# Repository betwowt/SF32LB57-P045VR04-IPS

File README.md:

# SF32LB57-P045VR04-IPS

SF32LB57 + P045VR04-IPS（480×854，ST7701S，RGB565，FT6236 触摸）显示工程。

面板的 3 线 SPI 初始化由 `H743_RGB_Adapter` 板上的 PY32F002 完成；SF32LB57
只负责 DPI RGB565 时序、背光（GPIO）、触摸 I2C 和 READY/复位握手。这个分工与
`H743_RGB_Adapter.pdf` 的 “04 - PY32 display initialization” 页一致。

```mermaid
flowchart LR
    SF[SF32LB57<br/>DPI RGB565 480×854] -->|RGB565 + PCLK/HS/VS/DE| AD[H743_RGB_Adapter<br/>40P host J1]
    SF -->|BL_PWM| AD
    SF -->|I2C1 SCL/SDA, CTP_INT, CTP_RST| AD
    SF -->|可选 READY 输入| AD
    AD -->|J2/J7 40P| PANEL[P045VR04-IPS<br/>ST7701S + FT6236]
    PY[PY32F002<br/>3-wire SPI init] -->|SCL/SDA/CS/RST| PANEL
    PY -->|READY| AD
```

## 1. 目录结构

```
SF32LB57-P045VR04-IPS/
├─ board/sf32lb57-p045vr04/       # 板级定义（基于 sf32lb57-lcd_n16r8_dpi）
│  ├─ hcpu/                       # HCPU board.conf / Kconfig / rtconfig / mem map
│  ├─ acpu/ lcpu/                 # 多核工程占位配置
│  ├─ bsp_*.c board.h bsp_board.h # 从 sf32lb57-lcd_base 复制并按需修改
│  ├─ ptab.json                   # Flash 分区
│  └─ SConscript                  # 编译板级文件 + 面板/触摸驱动
├─ drivers/panel/p045vr04.c       # ST7701S RGB565 DPI 驱动（不做 SPI 初始化）
├─ drivers/touch/ft6236.c         # FT6236 / FT6x36 触摸驱动（12-bit X/Y）
├─ app/project/                   # SiFli/RT-Thread 工程（scons 构建入口）
│  └─ proj.conf                   # RT-Thread / Wi-Fi / Opus / LVGL 选项
├─ app/src/main.c                 # xiaozhi 入口（Wi-Fi 联网 + UI/音频线程）
├─ app/src/xiaozhi/               # xiaozhi 应用层（WebSocket/MQTT、Opus+3A、LVGL UI）
├─ py32f002/P045VR04_Init/        # 适配板上 PY32F002 的 3 线 SPI 初始化固件
│  ├─ Src/ Inc/                   # ST7701S 初始化表 + 3 线 SPI + READY 握手
│  └─ MDK-ARM/ EIDE/              # 两套工程（共用同一份 Src/Inc）
├─ hardware/adapter-v2/          # H743_RGB_Adapter v2 的 KiCad 源文件
│  ├─ *.kicad_pro/_sch/_pcb      # 原理图(4 页层次) + PCB(78×75mm, 4 层)
│  └─ Adapter.* easyeda_convertlib.* docs/ scripts/
├─ patches/0001-add-p045vr04-panel.patch
├─ patches/0002-lcdc-dpi-linebuf-height.patch
├─ patches/0003-link-lds-ezip-font-sections.patch
├─ patches/0004-sdk-wifi-lwip-tls-tweaks.patch
└─ README.md
```

外部依赖（均不入库）：

| 依赖 | 放置位置 |
|---|---|
| [SiFli-SDK](https://github.com/OpenSiFli/SiFli-SDK)（本项目基于 `504eb222`） | 与本工程同级目录，或 `SIFLI_SDK` 指向它 |
| Puya **PY32F0xx_Firmware_V1.5.0**（HAL/CMSIS，仅 PY32 固件需要） | 本仓库根目录（与 `app/` 同级）；`py32f002` 的两个工程按 `../../../PY32F0xx_Firmware_V1.5.0` 引用 |
| Keil MDK + `Puya.PY32F0xx_DFP` 器件包（仅 MDK 工程需要） | 双击固件包 `Packs/MDK/*.pack` 安装 |

SF32 侧构建见第 4 节；PY32 侧构建见 `py32f002/P045VR04_Init/readme.txt`。

## 2. 面板与接口参数

| 项目 | 值 |
|---|---|
| 面板 | P045VR04-IPS，480×854，竖屏原生扫描 |
| 驱动 IC | ST7701S（RGB 接口，COLMOD=0x50 / RGB565） |
| 触摸 | FT6236，I2C 0x38，10-bit 坐标 |
| DPI 像素时钟 | 28 MHz（480×854 约 57.5 Hz） |
| 水平 | HSW=10，HBP=30，HFP=30 |
| 垂直 | VSW=4，VBP=15，VFP=12 |
| 颜色 | RGB565：R3..R7，G2..G7，B3..B7 |
| 背光 | PA_11（GPIO 高=全亮；该 pad 在本芯片上无 GPTIM 功能） |
| 触摸 I2C | I2C1：PA_22=SCL，PA_23=SDA |
| 触摸中断 | PA_20（`TOUCH_IRQ_PIN=20`） |
| 触摸复位 | AW9523 P1_6（`BSP_TP_Reset`） |
| 面板/PY32 复位 | AW9523 P1_7（`BSP_LCD_Reset`） |

> SF32LB57 的 LCDC 只输出 RGB565；下层未用的 R0..R2/G0..G1/B0..B2 由
> 适配器保持低电平，不做 RGB888 还原。

### 2.1 主控与存储（实测确认）

本板是 **SF32LB57GYD7N6**（QFN80）的 N16R16 变体，不是 N16R8：

| MPI | 器件 | 地址窗口 | 说明 |
|---|---|---|---|
| MPI1 | PSRAM 16 MB（OPSRAM，mode 3） | 0x60000000 | 双 RGB565 framebuffer 放在这里 |
| MPI2 | NOR Flash 16 MB | 0x12000000 | ftab / bootloader / 应用 |
| MPI3 | 无 | 0x14000000 | 未贴片，读回恒为 0xCC |

`board/sf32lb57-p045vr04/hcpu/Kconfig.board` 必须 `select SOC_SF32LB57GYD7N6`；
选成 `SOC_SF32LB57EYBBN6`（N16R8）会让构建把应用放到不存在的 MPI3，
表现为 `sftool write_flash` 返回成功但读回全 0xCC、板子不启动。

Flash 布局（`ptab.json` → 生成的 `ftab.bin`）：

| 区域 | 地址 |
|---|---|
| ftab | 0x12000000 |
| bootloader | 0x12010000（运行地址 0x20020000） |
| 应用 main | 0x12020000 |

## 3. 与 H743_RGB_Adapter 的接线

适配器 J1 是 **H743 板 LCD 座**的线序，不是 57 DevKit FPC1 的“正点原子
40P RGB”线序，两者不能直接对插。需要用一块 40P 0.5mm 转接板/交叉 FPC
按下表改线（或飞线）。J1 的完整定义见 `H743_RGB_Adapter.pdf` 第 1 页。

### 3.1 RGB565 与同步信号

| H743 适配器 J1 | 信号 | 57 DevKit FPC1（正点原子 40P） |
|---|---|---|
| 6 | R3 | 6 |
| 7 | R4 | 7 |
| 8 | R5 | 8 |
| 9 | R6 | 9 |
| 10 | R7 | 10 |
| 14 | G2 | 18 |
| 15 | G3 | 19 |
| 16 | G4 | 21 |
| 17 | G5 | 22 |
| 18 | G6 | 23 |
| 19 | G7 | 24 |
| 24 | B3 | 28 |
| 25 | B4 | 29 |
| 26 | B5 | 30 |
| 27 | B6 | 31 |
| 28 | B7 | 32 |
| 30 | PCLK | 33（PA_48） |
| 31 | HSYNC | 34（PA_49） |
| 33 | DE | 35（PA_50） |
| 32 | VSYNC | 36（PA_51） |

### 3.2 控制信号

| H743 适配器 J1 | 信号 | 57 DevKit 侧 | 固件配置 |
|---|---|---|---|
| 34 | BL_PWM | FPC1 PA_11（GPIO，无定时器功能） | `BSP_LCD_Backlight()` |
| 35 | CTP_RST | AW9523 P1_6 / 触摸座 RST | `BSP_TP_Reset()` |
| 36 | CTP_SDA | PA_23（I2C1_SDA） | `TOUCH_DEVICE_NAME="i2c1"` |
| 38 | CTP_SCL | PA_22（I2C1_SCL） | 同上 |
| 39 | CTP_INT | PA_20 | `TOUCH_IRQ_PIN=20` |
| 37 | H_LCD_READY | 任选空闲 GPIO | `CONFIG_LCD_READY_PIN=<pin>`；默认 -1 |
| 40 | H_NRST | FPC1 LCD_RST / AW9523 P1_7 | `BSP_LCD_Reset()` 释放 PY32 |

> 57 DevKit FPC1 的 37~40 脚在原理图上由 `BL_PWM / IOEX_CTP_RST /
> I2C_SDA / I2C_SCL / IOEX_LCD_RST` 五选四，具体顺序以 57x LCD-DevKit
> 原理图和 `ioconfig-08192026.xlsx` 为准。固件侧功能是固定的：PA_11 背光、
> PA_22/PA_23 为 I2C1、AW9523 P1_6 为触摸复位、P1_7 为面板/PY32 复位。
>
> 如果不接 READY，驱动会固定等待 1000 ms（PY32 约 500 ms 完成初始化）。
> 如果接 READY，在 `board.conf` 里加 `CONFIG_LCD_READY_PIN=xx` 重新编译。

**背光只能是 GPIO。** 57 的 pad 功能表里 `PAD_PA11` 只有
`GPIO_A11 / MPI3_CS2 / SD1_DIO1 / AUD_CLK_EXT`，**没有 GPTIM**；把它
`HAL_PIN_Set(..., GPTIM2_CH2, ...)` 会直接返回 -1，引脚停在复位态，
背光升压 SY7200 的 EN/PWM 悬浮，屏幕就偏暗。因此板级改为
`BSP_GPIO_Set(PA11, 0/1)`，与正点原子 H743 例程（PB5 直接拉高）等价。
`LCD_USING_PWM_AS_BACKLIGHT` 也已从面板 Kconfig 里去掉。

**RGB565 只走高 16 位，且 LCDC 的 16 位模式是低位对齐。** 适配器把
R0..R2 / G0..G1 / B0..B2 直接接地，只透传 R3..R7、G2..G7、B3..B7；而
LCDC 在 RGB565（`DPI_LCD_FORMAT=1`）下驱动的是 **R0..R4 / G0..G5 /
B0..B4**。因此 pad 上挂的功能要整体左移 3/2/3：

| FPC1（面板） | 57 pad | mux 的功能 |
|---|---|---|
| R3..R7 | PA_27..PA_31 | `LCDC1_DPI_R0`..`R4` |
| G2..G7 | PA_37..PA_42 | `LCDC1_DPI_G0`..`G5` |
| B3..B7 | PA_52、PA_53、PA_54、PA_46、PA_47 | `LCDC1_DPI_B0`..`B4` |
| R0..R2 / G0..G1 / B0..B2 | PA_24..PA_26 / PA_32..PA_33 / PA_43..PA_45 | 不用，保持 GPIO 输入 |

直连（`R0..R7` 一一对应）的写法会让每个通道只剩下中间几位，整屏发暗但
颜色不翻转——很容易被误判成背光不足。厂商自己的 LB57 DPI 参考板
（`sf32lb57-lcd_*_dpi`、`dpi-hdk_*_n16_dpi`）用的都是 24 位
`HTM_H070A20`，`SetColorMode()` 是空函数，RGB565 这条路没人验证过，
所以不能照抄它们的 mux。

时序脚：CLK=PA_48、HSYNC=PA_49、VSYNC=PA_51、DE=PA_50；
BL_PWM=PA_11（GPIO）；TP_INT=PA_20、TP_SDA/SCL=I2C1(PA_23/PA_22)、
TP_RST=AW9523 P1_6、LCD_RST=AW9523 P1_7。pad 对应关系与
`SF32LB57-DevKit-LCD-V1` 原理图（SCH_V1，2026-11-08）逐脚核对过。

### 3.3 电源

- 适配器 J1 的 +5V（1/2 脚）给适配器上的 SY7200 背光升压和 ME6211 3.3V
  LDO 供电；57 DevKit FPC1 的 1 脚也是 5V。
- 57 DevKit 与适配器必须共地；触摸和面板逻辑均为 3.3V。

## 4. 构建

### 4.1 准备 SDK

工程默认使用与当前目录同级的 `SiFli-SDK`：

```
Documents/project/
├─ SiFli-SDK/                     # https://github.com/OpenSiFli/SiFli-SDK
└─ SF32LB57-P045VR04-IPS/         # 本工程
```

面板选择项需要给 SDK 打一个很小的 Kconfig 补丁（只改
`customer/boards/Kconfig_lcd`，增加 `LCD_USING_P045VR04_IPS_DPI` 及
480×854 分辨率默认值）：

```bash
cd ../SiFli-SDK
git apply ../SF32LB57-P045VR04-IPS/patches/0001-add-p045vr04-panel.patch
```

当前工作区的 `SiFli-SDK` 已经应用该补丁。板级文件和驱动不在 SDK 内，
构建时通过 `--board_search_path` 引用，升级 SDK 不会覆盖它们。

小智的资源（emoji/天气 ezip 动画约 4.2 MB、DroidSansFallback TTF 约 3.9 MB）
放不进 7 MB 的应用分区，因此把二者分别链接到 `ROM2`/`ROM3`，再由
`ptab.json` 烧到独立地址。这需要给 LB57 的链接模板补两行 section 采集规则：

```bash
cd ../SiFli-SDK
git apply ../SF32LB57-P045VR04-IPS/patches/0003-link-lds-ezip-font-sections.patch
```

不打这个补丁时链接会报 `section .ROM3_IMG_EZIP.xxx will not fit in region ROM`。

最后是网络/音频的端口参数补丁（不碰 SDK 的库和断言，只调端口常量与两个
健壮性点）：

```bash
cd ../SiFli-SDK
git apply ../SF32LB57-P045VR04-IPS/patches/0004-sdk-wifi-lwip-tls-tweaks.patch
```

| 文件 | 改动 |
|---|---|
| `aic8800d40-n/platform/hal/sdio_port.c` | SDIO RX 缓冲 40 → 6 个 2 KB 块（40 × 2 KB ≈ 80 KB 内部堆放不下，会和 DPI 行缓冲抢内存）；SDIO 中断回调里先释放 MMC host 锁，避免 RX 回调取 `bus_txrx` 与 CMD52/CMD53 抢 host 锁形成 ABBA 死锁 |
| `aic8800d40-n/platform/netif/netif_port.c` | nocopy 模式 `NET_TXBUF_CNT` 10 → 28 槽：Opus 上行与 TTS 下行叠加时 10 槽会耗尽，随后 `altcp_write()` 失败直接关掉整条连接 |
| `drivers/Include/bf0_hal_conf_hcpu.h`、`bf0_hal_epic.h` | 允许用 `HAL_JPEGD_MODULE_DISABLE` 整体关闭 JPEG 解码器（`drv_gpu_open()` 无论是否解码都会预留约 31 KB 内部 SRAM），`EPIC_SUPPORT_JPEGD` 跟随该开关 |
| `rtos/rtthread/bsp/sifli/drivers/drv_sdio.h` | `SDIO_BUFF_SIZE` 65024 → 8 KB：bounce 池与 `max_seg_size` 一起收缩，段大小与池一致所以不会越界；需要时可外部覆盖 |
| `lwip .../apps/websocket/websocket_client.c` | `altcp_write()` 返回 `ERR_MEM` 时归还 pbuf 交给调用者重试，不再一遇拥塞就断连接；每秒最多打印一次 `WS_TX_STALL` 现场 |
| `lwip .../core/tcp.c` | 新增 `tcp_dbg_dump()`，打印所有 active pcb 的窗口、重传、队列状态，用于定位上行停滞 |
| `external/mbedtls_228/ports/src/tls_certificate.c` | 追加 16 张根证书（COMODO/Sectigo 等），`wss://api.tenclass.net` 的握手才能通过校验 |

### 4.2 激活 SiFli 编译环境

使用 SDK 自带的环境管理器（`uv`）激活 gcc 工具链和 scons：

```bash
cd ../SiFli-SDK
. ./export.sh
```

或在 PowerShell 中：

```powershell
cd ..\SiFli-SDK
. .\export.ps1
```

> 如果 `export.sh` 在当前 Git Bash 下因 `uv` 的 Windows 路径报
> `\\?\...` 错误，可直接使用 SDK 环境里已经安装好的
> `...\.sifli\envs\default\<hash>\python\Scripts\scons.exe` 和
> `...\.sifli\tools\arm-none-eabi-gcc\14.2.1\bin`，并设置
> `SIFLI_SDK`、`RTT_CC=gcc`、`RTT_EXEC_PATH`。本工程已用这种方式
> 完成编译验证。

### 4.3 编译

```bash
cd SF32LB57-P045VR04-IPS/app/project
scons --board=sf32lb57-p045vr04 \
      --board_search_path=../../board -j 8
```

或直接运行工程根目录的脚本：

```powershell
.\build.ps1
```

```bash
./build.sh
```

`build.ps1` 已在 PowerShell 下完成端到端验证；`build.sh` 请在
Git Bash 中使用（WSL 的 bash 看不到 Windows 的 `.sifli` 环境）。
两个脚本都会在未激活环境时自动查找 `~/.sifli` 下的 scons 和 gcc。

输出在 `app/project/build_sf32lb57-p045vr04_hcpu/`：

| 文件 | 说明 |
|---|---|
| `main.bin/ER_IROM1.bin` | 应用镜像（烧到 0x12020000，≤ 0x300000） |
| `main.bin/ER_IROM2.bin` | emoji/天气 ezip 资源（烧到 0x12320000，≤ 0x440000） |
| `main.bin/ER_IROM3.bin` | DroidSansFallback TTF（烧到 0x12760000，2 MB 扇区对齐到 0x400000） |
| `bootloader/bootloader.bin` | bootloader 镜像（烧到 0x12010000） |
| `ftab/ftab.bin` | 分区表，内含 bootloader/app 的地址与长度（烧到 0x12000000） |
| `sftool_param.json` | sftool UART 下载参数（5 个镜像，地址已按 N16R16 生成） |

编译后的关键配置可在 `build_sf32lb57-p045vr04_hcpu/rtconfig.h` 中确认：

```
#define LCD_HOR_RES_MAX 480
#define LCD_VER_RES_MAX 854
#define BSP_LCDC_USING_DPI 1
#define BSP_USING_RAMLESS_LCD 1
#define BSP_USING_TOUCHD 1
#define TOUCH_IRQ_PIN 20
```

### 4.4 烧录（UART / sftool，实测通过）

`download.bat` 走 J-Link，本工程不用；用 sftool 从 CH343P 的串口下载即可。

1. USB Type-C 连接 57 DevKit 的 **USB-to-UART**（CH343P，本机为 COM8）；
2. 按 57 DevKit 用户指南进入下载模式（BOOT 跳线），复位；
3. 在 `app/project/build_sf32lb57-p045vr04_hcpu/` 下执行：

```bat
sftool -c SF32LB57 -m nor -p COM8 write_flash --verify ^
    bootloader\bootloader.bin@0x12010000 ^
    main.bin\ER_IROM1.bin@0x12020000 ^
    main.bin\ER_IROM2.bin@0x12320000 ^
    main.bin\ER_IROM3.bin@0x12760000 ^
    ftab\ftab.bin@0x12000000
```

也可以直接用生成的参数文件：

```bat
sftool -c SF32LB57 -m nor -p COM8 config sftool_param.json
```

4. 去掉 BOOT 跳线，复位（或重新上电）从 Flash 启动；应用的 RT-Thread
   控制台在 **UART1 / 1000000 8N1**，即同一个 CH343 口。

> 若 `write_flash` 打印 "verify failed"：先确认 `sftool_param.json` 里的
> 五个地址都在 0x1200_0000 段（N16R16/MPI2），而不是 0x1400_0000（N16R8/MPI3）。
> 地址错了写入会被静默丢弃，读回全是 0xCC。

独立校验（不经 sftool 的 CRC 逻辑）：

```bat
sftool -c SF32LB57 -m nor -p COM8 read_flash ftab_rb.bin@0x12000000:0x2C18
sftool -c SF32LB57 -m nor -p COM8 read_flash main_rb.bin@0x12020000:377388
fc /b ftab_rb.bin ftab\ftab.bin
fc /b main_rb.bin main.bin
```

## 5. 演示（GE demo 移植版）

`app/src/main.c` 现在运行 ArtInChip GE demo 的 SF32LB57 移植版（51 个
过程化特效，源自公开的 ArtInChip GE demo / ESP32-S31 移植，Unlicense），
不再使用 LVGL。
`app/src/ge_demo/` 的结构（特效代码的许可文本见 `app/src/ge_demo/LICENSE`）：

| 文件 | 作用 |
|---|---|
| `ge_compat.c` | ArtInChip `mpp_ge` API → SiFli EPIC：fill / bitblt（缩放、镜像、alpha）/ rotate（任意角）；ADD/XOR/色键在 CPU 端回退；505 px 分块 |
| `demo_entry.c` | 480×854 RGB565 双 PSRAM 缓冲、10 s 自动切换、PA34 按键、shell 命令、LCDC `draw_rect` 呈现 |
| `effects/*.c` | 51 个特效，`effect_registry.c` 显式注册（不依赖 linker section） |

显示通路：CPU 生成 240×427 RGB565/YUV400 纹理 → EPIC 缩放到 480×854 →
双缓冲；LCDC PTC 连续扫描，`draw_rect` 切换缓冲。纹理 arena 为 4 MB
PSRAM（`ge_compat.c` 的 `s_ge_heap_mem`），framebuffer 为两块 819,840 B
+ 2 KB guard 的 PSRAM。LVGL 已从 `proj.conf` 移除，省下 1.64 MB
framebuf 和 128 KB 内存池。

控制：

| 输入 | 动作 |
|---|---|
| PA34 按键（上升沿） | 下一个特效 |
| `demo_next` / `demo_prev` | 下一个 / 上一个 |
| `demo_jump <n>` | 跳到第 n 个（0 起） |
| `demo_list` | 列出全部特效 |

每 10 s 自动切换。EPIC 没有 DE 的 CCM/GAMMA/HSBC，`mpp_fb_ioctl` 为空实现，
依赖这些色彩矩阵的特效只保留几何/混合部分；ADD、XOR、色键由 CPU 完成。

## 6. 与 H743 工程的差异

| 项目 | `正点原子h743-P045VR04-IPS` | 本工程 |
|---|---|---|
| 主控 | STM32H743 LTDC | SF32LB57 LCDC DPI |
| 面板初始化 | PY32F002 3-wire SPI | 同一块适配器上的 PY32F002 |
| 颜色 | RGB565 | RGB565 |
| 触摸 | H743 软件 I2C + FT5206 | SF32 I2C1 + FT6236 |
| 背光 | PB5（GPIO 拉高） | PA_11（GPIO 拉高） |
| READY | PG3 输入 | 可选 GPIO（默认固定延迟） |

## 7. 注意事项

1. **不要**在 SF32 侧调用 `BSP_LCD_Reset()` 去复位面板：适配器 J1 的
   RESET 脚接的是 PY32 的 NRST，拉低会把初始化 MCU 一起复位。当前
   `p045vr04.c` 的 `LCD_Init()` 不调用它，只等待 READY/固定延迟。
2. 适配器上的 PY32 必须烧录 **P045VR04 对应** 的固件（`py32f002/
   P045VR04_Init/`，`PANEL_MAP_P045VR04`），否则面板不会出图。
3. RGB565 是硬件决定的：适配器只连了 R3..R7/G2..G7/B3..B7，PY32 也把
   COLMOD 设为 0x50。应用层不要切到 RGB888。
4. 57 DevKit FPC1 的 37~40 脚定义请以实物原理图为准；如果线序与上表
   不同，只需改转接板/飞线，固件侧的 PA_11、PA_22、PA_23、PA_20、
   AW9523 P1_6/P1_7 不变。
5. 如果使用 57 DevKit 自带的其他 RGB 屏（如 HTM-H070A20），把
   `board.conf` 的 `CONFIG_LCD_USING_P045VR04_IPS_DPI=y` 换成对应面板
   选项即可；本工程的 `p045vr04` 驱动只适用于 480×854 ST7701S。

## 8. 已验证（GE demo / 面板链路）

工具链：SiFli SDK `504eb222`、arm-none-eabi-gcc 14.2.1、scons 4.10.1，
`build.ps1` 在 PowerShell 下端到端通过。

硬件配置（实测确认）：SF32LB57GYD7N6 / N16R16，`CONFIG_SOC_SF32LB57GYD7N6=y`、
`BSP_QSPI1_MODE=3`（PSRAM 16 MB）、`BSP_QSPI2_MODE=0`（NOR 16 MB）、
`BSP_ENABLE_MPI3` 关闭。

| 项目 | 结果 |
|---|---|
| 镜像 | `main.bin` 377,388 B（GE demo + EPIC + 51 特效），`ftab` base 0x12000000，应用 0x12020000 |
| 烧录 | `sftool -c SF32LB57 -m nor -p COM8 write_flash --verify`，三块镜像逐字节读回一致 |
| 显示 | DPI RGB565，480×854；`Found lcd p045vr04 id:4585h` → `display on` |
| DPI 颜色 | 16 位输出为低位对齐，pad 上的功能左移 3/2/3 后才与适配器的高 16 位对齐（见 3.2） |
| 背光 | PA_11 只能当 GPIO（无 GPTIM 功能），`BSP_LCD_Backlight()` 拉高升压 EN |
| 面板/LCDC | 上一版 LVGL 固件实测正常；本版 `drv_lcd` / `p045vr04` 未改 |
| GE demo | 已实测（COM8）：51 个特效正常显示并 10 s 自动切换；XOR/色键/旋转 ADD 软件回退正常；OSD 已关闭 |
| 触摸 | `ft6236` 被探测到并注册为 `touch` 设备；点按/拖动均有串口日志，坐标落在手指位置 |

GE demo 已关闭 OSD（不再显示 CPU/FPS/RAM）；触摸驱动仍保留，但当前演示不读取触摸。

## 9. 小智 AI（xiaozhi）移植

协议与业务层来自 [78/xiaozhi-esp32](https://github.com/78/xiaozhi-esp32)，
网络传输改为 **Wi-Fi**（板载 AIC8800D40LS-N，SDIO2），不再使用上游 LB52 的
BLE PAN 方案。

### 9.1 外设清单

| 功能 | 本板实现 |
|---|---|
| 显示 | DPI RGB565 480×854，P045VR04-IPS（ST7701S），PY32F002 完成 SPI 初始化 |
| 触摸 | FT6236，I2C1（PA22/PA23，INT PA20） |
| 音频 | 片内 AUDCODEC + AUDPRC（`CONFIG_BSP_ENABLE_AUD_CODEC/AUD_PRC`），Opus 编解码 + WebRTC 3A |
| 按键 | PA34 单键，普通 GPIO 上拉有效（对话/唤醒） |
| 网络 | AIC8800D40N Wi-Fi（`CONFIG_AIC_WLAN_AIC8800D40N`），SDIO2 |
| IO 扩展 | AW9523B：LCD_RST、CTP_RST、PA_EN、Wi-Fi 电源/唤醒 |
| 电源 | USB 供电，无充电器；充电检测回调改为固定“在充电”状态 |

无蓝牙协议栈：`bts2_*`/`bt_env.h`/`dfu_pan_ota` 依赖已全部移除，
`g_pan_connected` 仅作为“网络就绪”标志使用。

### 9.2 代码结构

```
app/src/main.c                  # 启动 UI 线程 + Wi-Fi 线程；网就绪后注册设备、启动按键
app/src/xiaozhi/
├─ xiaozhi_websocket.c/.h       # WebSocket 会话、Opus 收发、重连
├─ xiaozhi_mqtt.c               # MQTT+UDP 传输（CONFIG_XIAOZHI_USING_MQTT）
├─ xiaozhi_audio.c              # 采集/播放、AEC/VAD 接入
├─ xiaozhi_ui.c / _screen.c     # LVGL v9 对话界面、TinyTTF 中文
├─ xiaozhi_client_public.c      # 设备 ID/激活/OTA 上报
├─ iot/ mcp/ kws/ weather/      # IoT 描述、MCP、离线唤醒、天气/时间
└─ board/                       # 板级适配（按键、亮度、功放）
```

Wi-Fi 凭据在 `app/project/Kconfig.proj` 的 `XZ_WIFI_SSID` / `XZ_WIFI_PASSWORD`
配置，也可运行时执行 `xz_wifi_join <ssid> [password]`。

### 9.3 构建结果

`build.ps1` 端到端通过（arm-none-eabi-gcc 14.2.1），生成 5 个镜像：

| 镜像 | 大小 | 烧录地址 |
|---|---|---|
| `main.bin/ER_IROM1.bin` | 2,287,344 B | 0x12020000 |
| `main.bin/ER_IROM2.bin`（emoji/天气 ezip） | 4,190,922 B | 0x12320000 |
| `main.bin/ER_IROM3.bin`（中文 TTF） | 3,939,852 B | 0x12760000 |
| `bootloader/bootloader.bin` | 40,252 B | 0x12010000 |
| `ftab/ftab.bin` | 11,288 B | 0x12000000 |

资源与字体的符号地址已用 `nm main.elf` 核对落在各自区间
（`crying_5_map`→0x12419EC4，`xiaozhi_font`→0x12760000）。

### 9.4 当前状态

- 构建：通过（含 LVGL v9、TinyTTF、mbedTLS、Opus/WebRTC、AIC8800 驱动）。
- 硬件：屏幕/触摸链路由第 8 节 GE demo 实测过；小智固件的 Wi-Fi 关联、
  WebSocket 会话与音频回声尚未在本轮实测，烧录后需按串口日志确认
  `xz: app_wlan_sta_start ret=...`、`session ready` 与麦克风/扬声器电平。

### 9.5 圆脸 UI 的绘制约定

EPIC 的圆角填充与圆角粗线路径在这块屏上会画出缺口、虚线和撕裂边缘，小尺寸
图形尤其明显。所以 `xiaozhi_ui.c` 把眼睛、腮红、嘴和状态栏图标全部改成
**CPU 光栅化 → RGB565 纹理 → `lv_image` 平铺**：

| 元素 | 纹理 | 说明 |
|---|---|---|
| 背景大圆 + 辉光 | (380+2×36)² | 4 个同心圆一次烘焙 |
| 眼睛 / 腮红 / 开口嘴 | 56×56 | 同一张 disc 纹理，靠 `LV_IMAGE_ALIGN_STRETCH` 变形 |
| 闭嘴 smile/frown/flat | 100×40 ×3 | `tex_polyline()`：圆头粗线，4×4 超采样 |
| 信号 / 电池壳 / 电池填充 | 44×22、60×28、48×20 | `tex_rrect()`：4×4 超采样圆角矩形 |

约束与坑：

- 每种视觉变体各占一张**不可变**纹理，运行时只切 `lv_image_set_src`。
  LVGL 按 src 指针缓存解码结果，原地改写缓冲区会读到旧像素。
- `seg_dist2()` 的距离公式里 `t*t` 在 1/8 像素坐标下可达 1e10，**必须用
  `int64_t`**。用 `long`（Cortex-M33 上是 32 位）会溢出，表现为嘴中间被挖掉
  十几像素的缺口；长直段（flat）必定出现，弯曲的 smile/frown 反而看不出来。
- 纹理缓冲区放在 `xz_ui_tex` 段（PSRAM），写完调用 `SCB_CleanDCache_by_Addr`。
- 验证：串口执行 `xz_face idle|error|listen|speak|...` 固定状态，再用
  `xz_shot` 导出 LCD 扫描缓冲（480×854 RGB565 hex）或 `xz_snap` 导出 LVGL
  截图，主机侧按 `偏移:hex XOR` 行格式重建 PNG 比对。

### 9.6 Listening/Thinking 圆环

`lv_arc` 的 EPIC 实现会画成一段段阶梯状虚线，而且每帧 `lv_malloc` 一块掩码
缓冲（426 px 宽时约 3.4 KB，30 Hz）——在本机只剩约 40 KB 的堆上会加速碎片化。
所以圆环同样改成软件绘制：

- `backdrop_rgb8()` 把"同心辉光盘"抽成按像素求值的函数，背景大图与圆环共用，
  保证颜色逐像素一致。
- `ring_blit()` 直接在 `face_pixels` 里混合/还原 70° 环带（只碰环带约 2.5k 个
  像素），`ring_update()` 先擦掉上一帧角度再画新角度，`ring_clear()` 在离开
  Listening/Thinking 时擦净；随后只 `lv_obj_invalidate(backdrop_obj)`。
- 颜色 `COL_RING` / `COL_RING_THINK` 直接混入，不再依赖 recolor 或 arc 样式。

实测：圆弧平滑、按角度旋转（质心随帧移动）、切走后无残留，动画期间堆不增长、
无 `malloc fail`。

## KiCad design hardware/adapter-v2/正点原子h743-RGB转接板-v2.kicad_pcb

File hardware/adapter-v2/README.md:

# H743 RGB 屏幕转接板

本目录是可直接打开的 **KiCad 10** 项目。当前交付范围为 **原理图、项目内符号/封装、PCB 元件布局**，不含 PCB 布线、生产文件或屏幕初始化固件。

打开 `正点原子h743-RGB转接板-v2.kicad_pro`。主原理图为 `正点原子h743-RGB转接板-v2.kicad_sch`，PCB 为同名 `.kicad_pcb`。原理图 PDF 和检查报告在 `output/`。

## 本仓库收录范围

只收录设计源文件：工程/原理图/PCB、项目库（`Adapter.*`、`easyeda_convertlib.*`）、
`docs/`、`scripts/`、原理图 PDF。以下目录为生成物或第三方资料，未入库：

| 未入库 | 说明 |
|---|---|
| `output/`、`Gerber/`、`*Gerber.zip`、`bom/` | 由 KiCad 重新导出 |
| `.history/`、`backups/`、`tmp/` | KiCad 自动备份 |
| `references/` | 厂商 datasheet（AP2112 / PY32F002A / SY7200A 等），自行下载 |

## 已采用的方案

- J1：正点原子 H743 开发板 RGB 接口，40Pin、0.5mm，按提供的图 1 编号。
- J2：图 2 的屏幕线序；J7：图 3 的屏幕线序。**两个独立插座，各自固定接线**。
- 实际是 **五款屏幕、两种接口线序**。按所插屏幕手动刷写对应的 PY32 初始化程序，没有屏幕选择跳线、自动识别或通用初始化程序。
- 两个屏幕座共用 RGB、SPI、复位和背光电路，**一次只接一块屏幕**。三个触摸座也一次只接一个。
- RGB565 的 16 根有效数据线及 PCLK/HSYNC/VSYNC/DE 共用 5 组 **33Ω×4 独立排阻**，0603×4 / 3216 封装，参考料号 CAY16-330J4LF。每组内部四路互相独立，不能换成共端排阻。
- PY32F002AW15S，SOP16；PA0=SCK、PA1=SDA、PA2=CS、PA3=RESET。这些是 GPIO 软 SPI 分配，不依赖硬件 SPI 复用。
- AP2112K-3.3 从开发板 5V 产生本板 3.3V；背光参考 T113_MIPI_Adapter 的最终版本，采用 SY7200ABC、4.7µH、SS14、5.1Ω 采样。L1 使用参考工程已确认的 2.5×2.0mm C5832360 封装，反馈电阻值保持不变。
- PA6 的 READY 信号控制背光许可，并送到 H743 PG3。上电未初始化时背光关闭；初始化程序完成后应把 PA6 拉高。

## 文件索引

| 文件 | 用途 |
|---|---|
| `正点原子h743-RGB转接板-v2.kicad_sch` | 开发板接口、RGB 排阻、层次页入口 |
| `02_LCD_Touch.kicad_sch` | 两个屏幕座、三个触摸座 |
| `03_Power_Backlight.kicad_sch` | 3.3V、背光升压、背光使能 |
| `04_PY32_Init.kicad_sch` | PY32、复位、软 SPI、SWD |
| `Adapter.kicad_sym` | 项目自带符号库 |
| `Adapter.pretty/` | 项目自带封装库 |
| `sym-lib-table` / `fp-lib-table` | 使用 `${KIPRJMOD}` 的相对库路径 |
| `docs/design_notes.md` | 完整接线、封装依据、未确认参数 |
| `docs/BOM.csv` | BOM；元件值和待确认项 |
| `docs/connector_pinout.csv` | 各连接器逐脚网络 |
| `docs/verification.md` | 验证范围和结果 |

## PCB 布局

当前板框 **78×75mm**，4 层规划；板框尺寸和安装方式为本次布局的暂定值，尚无外壳/孔位约束。J1 从左侧插入，两个屏幕座在右侧上下排列，三个触摸座沿上边排列，PY32/SWD 位于下方。左上是 LDO，右上是背光升压。

5 组 RGB 排阻放在 J1 后方，中央留走线空间。本阶段无走线、无过孔、无铺铜。DRC 中的未连接项是保留的飞线，不应据此误认为可以直接制板。

## 确认边界

用户已确认三个 40Pin 接口间距均为 0.5mm；还没有提供五款屏幕完整规格、背光串并联关系/电流、排线厚度及开发板至本板排线的同面/异面关系。当前封装采用有资料的 Omron XF2M 双面接触座候选，**不能仅凭 40Pin/0.5mm 判断实际排线完全适配**。具体边界见 `docs/design_notes.md`。

脚本仅供复现。手动编辑 KiCad 文件后不要重新运行生成脚本，否则会覆盖设计。`scripts/build_project.py` 生成原理图，`scripts/build_pcb.py` 需要使用 KiCad 自带 Python，并在它之前导出 XML 网表。

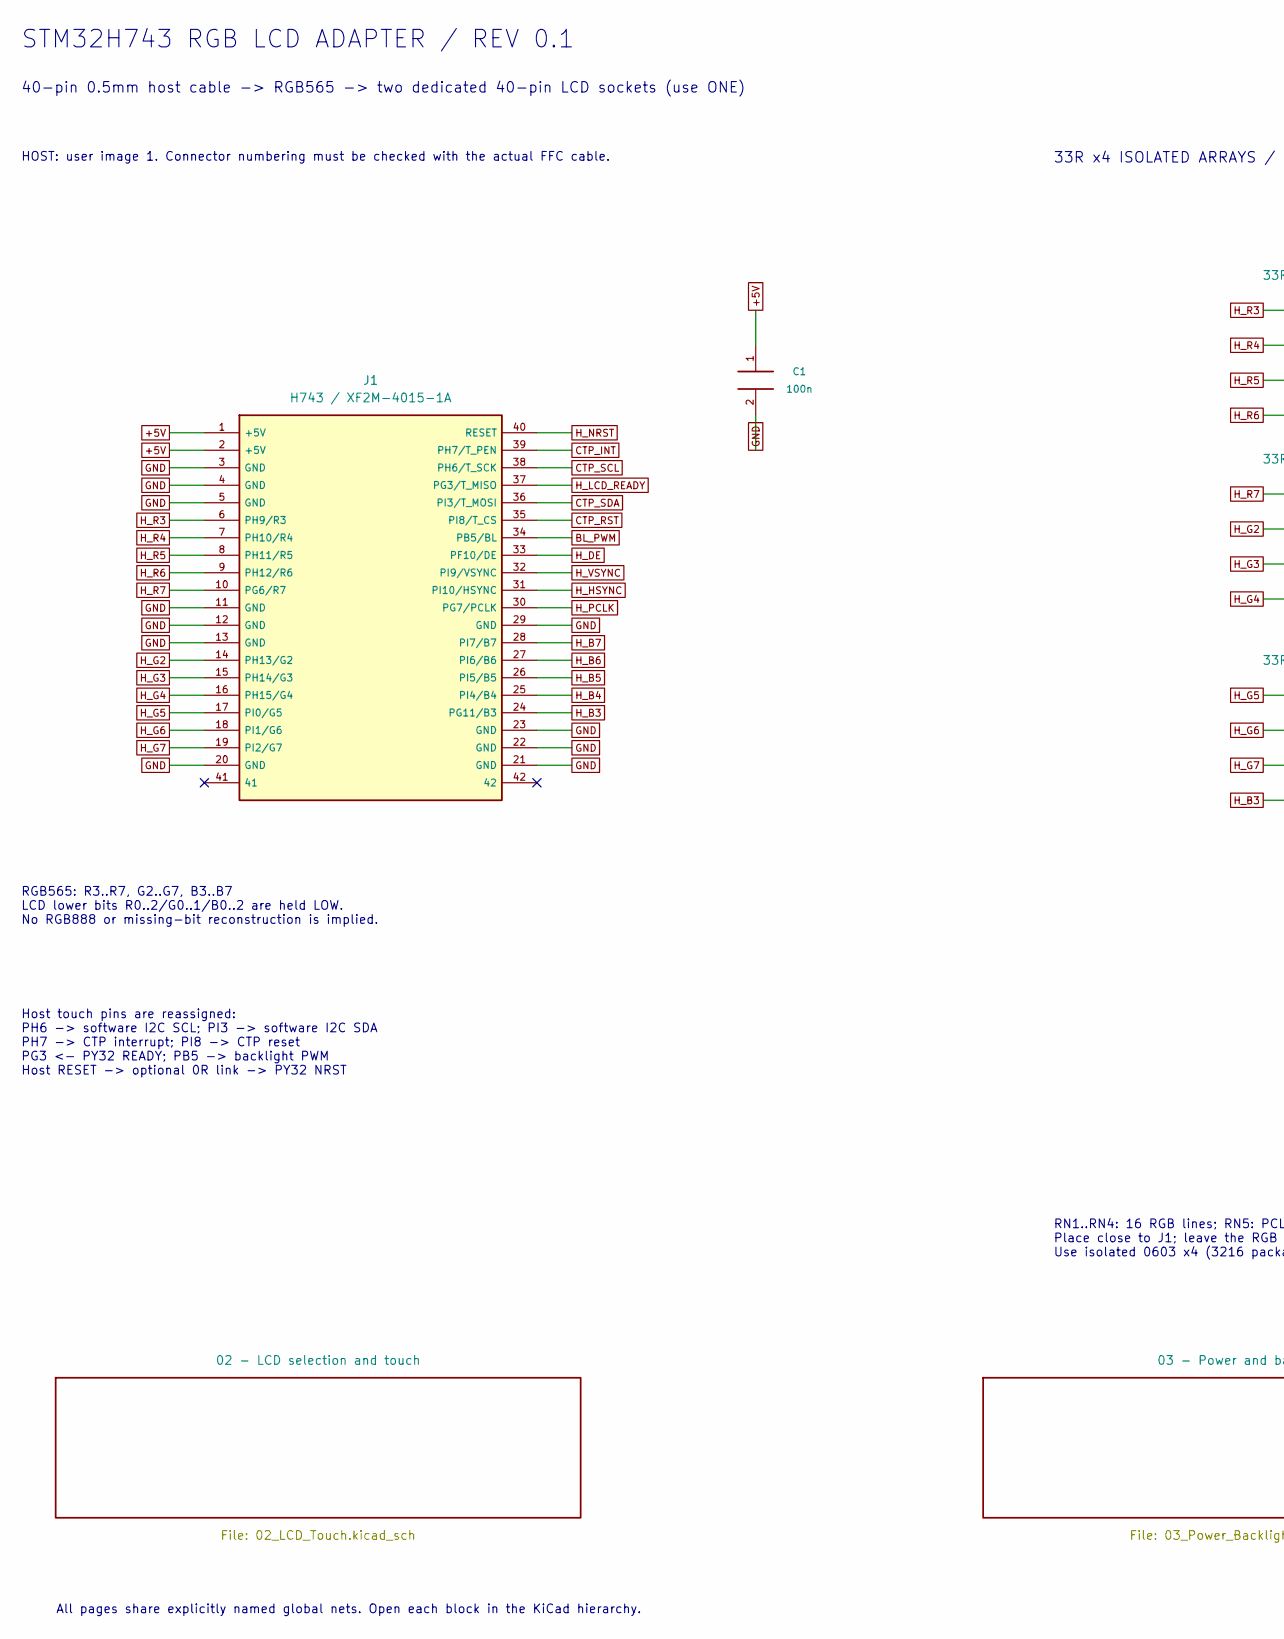
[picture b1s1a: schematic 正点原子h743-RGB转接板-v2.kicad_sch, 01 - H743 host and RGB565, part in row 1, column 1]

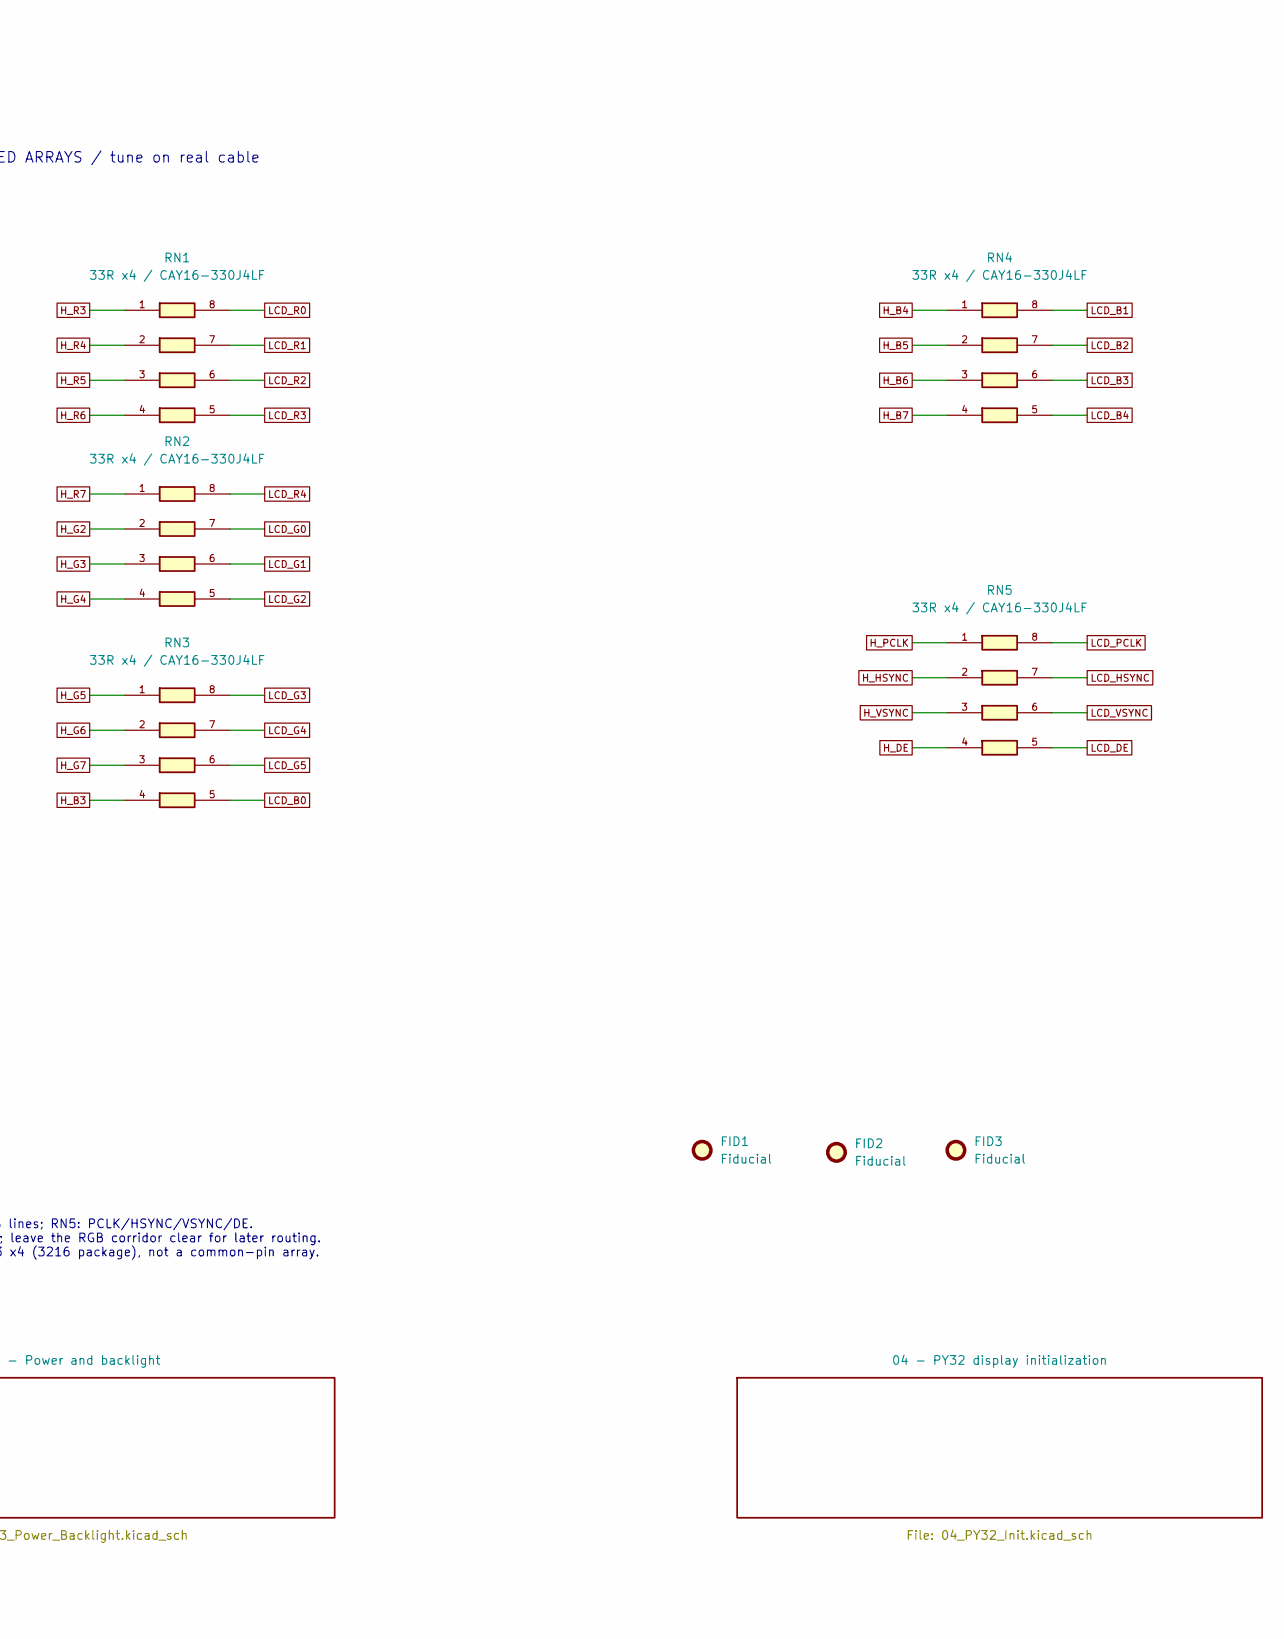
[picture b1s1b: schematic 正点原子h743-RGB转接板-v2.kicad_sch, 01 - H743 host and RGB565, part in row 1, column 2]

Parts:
C1: 100n; C_0603_1608Metric
FID1, FID2, FID3: Fiducial; Fiducial_1mm_Mask2mm
J1: H743 / XF2M-4015-1A; FPC-SMD_AFC01-S40FCA-00
RN1, RN2, RN3, RN4, RN5: 33R x4 / CAY16-330J4LF; R_Array4_0603

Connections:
+5V: C1.1, J1.1 (+5V), J1.2 (+5V); also elsewhere on the board
BL_PWM: J1.34 (PB5/BL); also elsewhere on the board
CTP_INT: J1.39 (PH7/T_PEN); also elsewhere on the board
CTP_RST: J1.35 (PI8/T_CS); also elsewhere on the board
CTP_SCL: J1.38 (PH6/T_SCK); also elsewhere on the board
CTP_SDA: J1.36 (PI3/T_MOSI); also elsewhere on the board
GND: C1.2, J1.3 (GND), J1.4 (GND), J1.5 (GND), J1.11 (GND), J1.12 (GND), J1.13 (GND), J1.20 (GND), J1.21 (GND), J1.22 (GND), J1.23 (GND), J1.29 (GND); also elsewhere on the board
H_B3: J1.24 (PG11/B3), RN3.4
H_B4: J1.25 (PI4/B4), RN4.1
H_B5: J1.26 (PI5/B5), RN4.2
H_B6: J1.27 (PI6/B6), RN4.3
H_B7: J1.28 (PI7/B7), RN4.4
H_DE: J1.33 (PF10/DE), RN5.4
H_G2: J1.14 (PH13/G2), RN2.2
H_G3: J1.15 (PH14/G3), RN2.3
H_G4: J1.16 (PH15/G4), RN2.4
H_G5: J1.17 (PI0/G5), RN3.1
H_G6: J1.18 (PI1/G6), RN3.2
H_G7: J1.19 (PI2/G7), RN3.3
H_HSYNC: J1.31 (PI10/HSYNC), RN5.2
H_LCD_READY: J1.37 (PG3/T_MISO); also elsewhere on the board
H_NRST: J1.40 (RESET); also elsewhere on the board
H_PCLK: J1.30 (PG7/PCLK), RN5.1
H_R3: J1.6 (PH9/R3), RN1.1
H_R4: J1.7 (PH10/R4), RN1.2
H_R5: J1.8 (PH11/R5), RN1.3
H_R6: J1.9 (PH12/R6), RN1.4
H_R7: J1.10 (PG6/R7), RN2.1
H_VSYNC: J1.32 (PI9/VSYNC), RN5.3
LCD_B0: RN3.5; also elsewhere on the board
LCD_B1: RN4.8; also elsewhere on the board
LCD_B2: RN4.7; also elsewhere on the board
LCD_B3: RN4.6; also elsewhere on the board
LCD_B4: RN4.5; also elsewhere on the board
LCD_DE: RN5.5; also elsewhere on the board
LCD_G0: RN2.7; also elsewhere on the board
LCD_G1: RN2.6; also elsewhere on the board
LCD_G2: RN2.5; also elsewhere on the board
LCD_G3: RN3.8; also elsewhere on the board
LCD_G4: RN3.7; also elsewhere on the board
LCD_G5: RN3.6; also elsewhere on the board
LCD_HSYNC: RN5.7; also elsewhere on the board
LCD_PCLK: RN5.8; also elsewhere on the board
LCD_R0: RN1.8; also elsewhere on the board
LCD_R1: RN1.7; also elsewhere on the board
LCD_R2: RN1.6; also elsewhere on the board
LCD_R3: RN1.5; also elsewhere on the board
LCD_R4: RN2.8; also elsewhere on the board
LCD_VSYNC: RN5.6; also elsewhere on the board

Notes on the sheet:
HOST: user image 1. Connector numbering must be checked with the actual FFC cable.
40-pin 0.5mm host cable -> RGB565 -> two dedicated 40-pin LCD sockets (use ONE)
RN1..RN4: 16 RGB lines; RN5: PCLK/HSYNC/VSYNC/DE. Place close to J1; leave the RGB corridor clear for later routing. Use isolated 0603 x4 (3216 package), not a common-pin array.
RGB565: R3..R7, G2..G7, B3..B7 LCD lower bits R0..2/G0..1/B0..2 are held LOW. No RGB888 or missing-bit reconstruction is implied.
STM32H743 RGB LCD ADAPTER / REV 0.1
33R x4 ISOLATED ARRAYS / tune on real cable
All pages share explicitly named global nets. Open each block in the KiCad hierarchy.
Host touch pins are reassigned: PH6 -> software I2C SCL; PI3 -> software I2C SDA PH7 -> CTP interrupt; PI8 -> CTP reset PG3 <- PY32 READY; PB5 -> backlight PWM Host RESET -> optional 0R link -> PY32 NRST

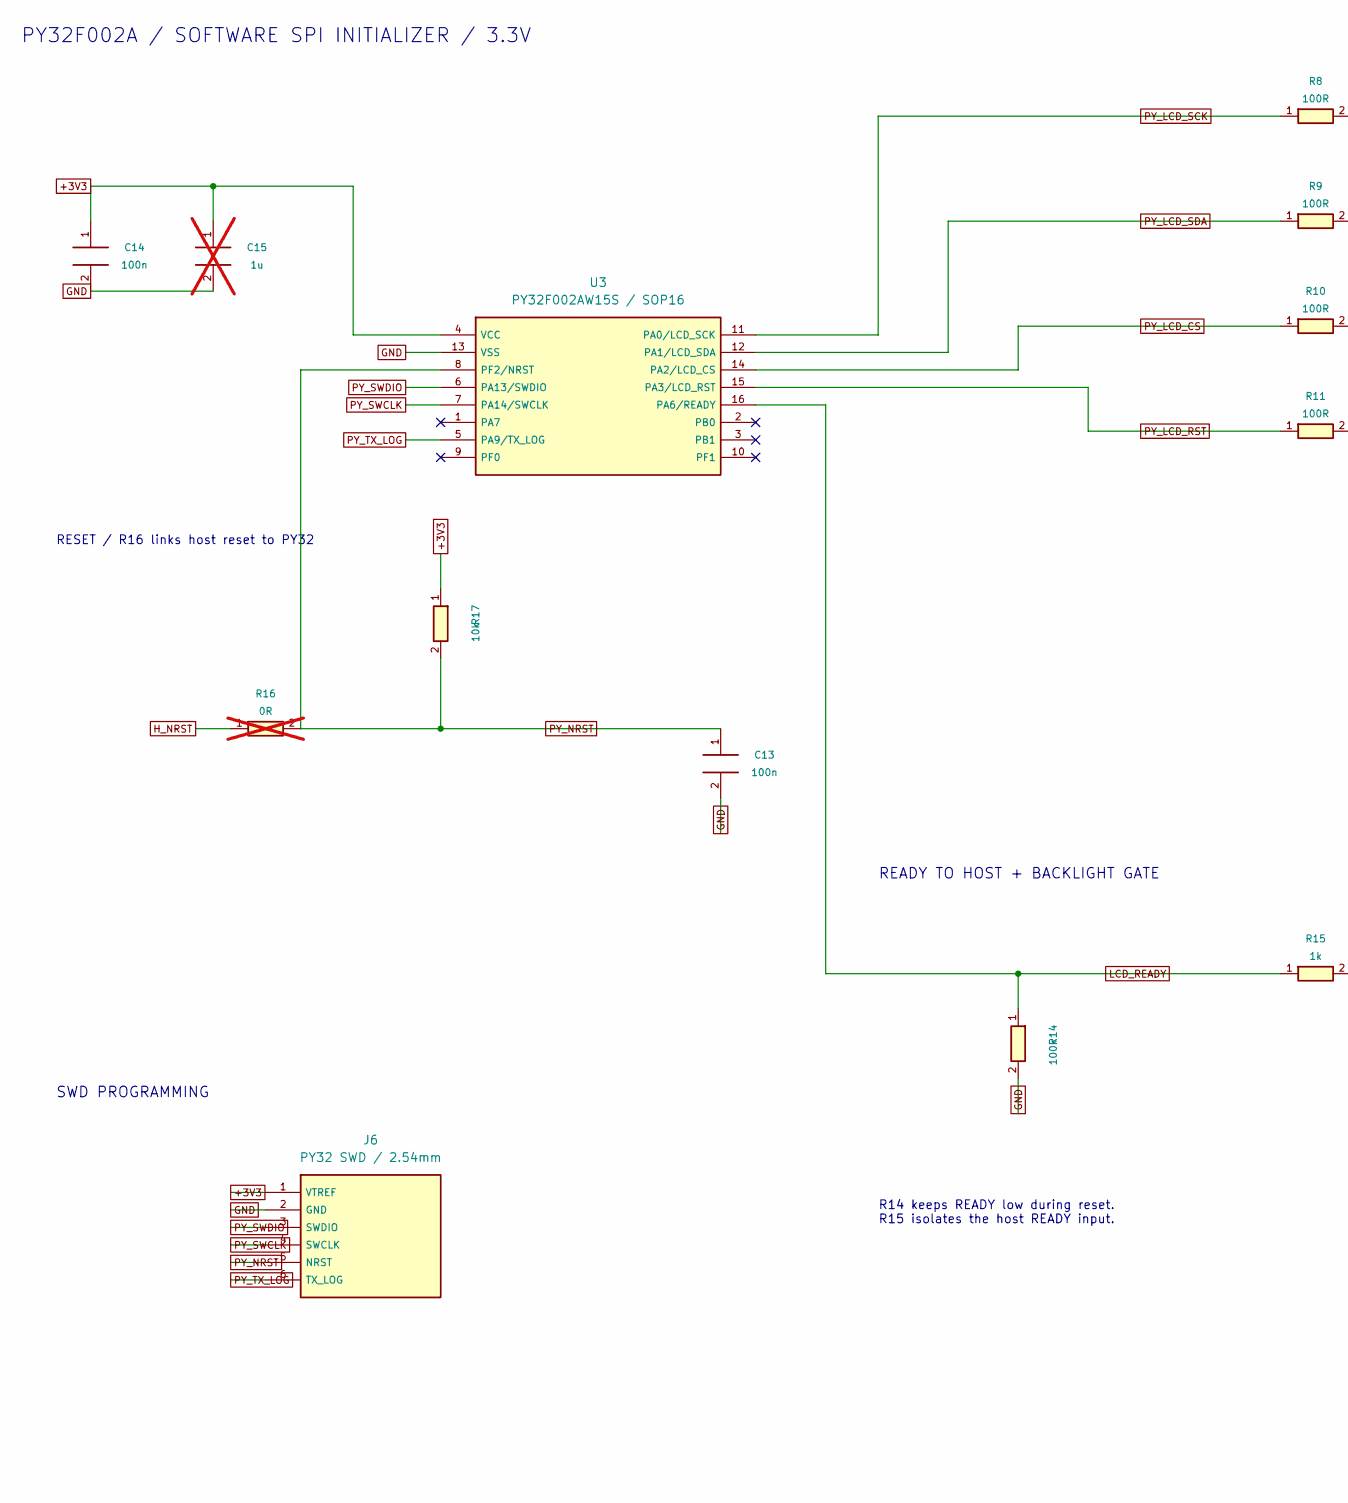
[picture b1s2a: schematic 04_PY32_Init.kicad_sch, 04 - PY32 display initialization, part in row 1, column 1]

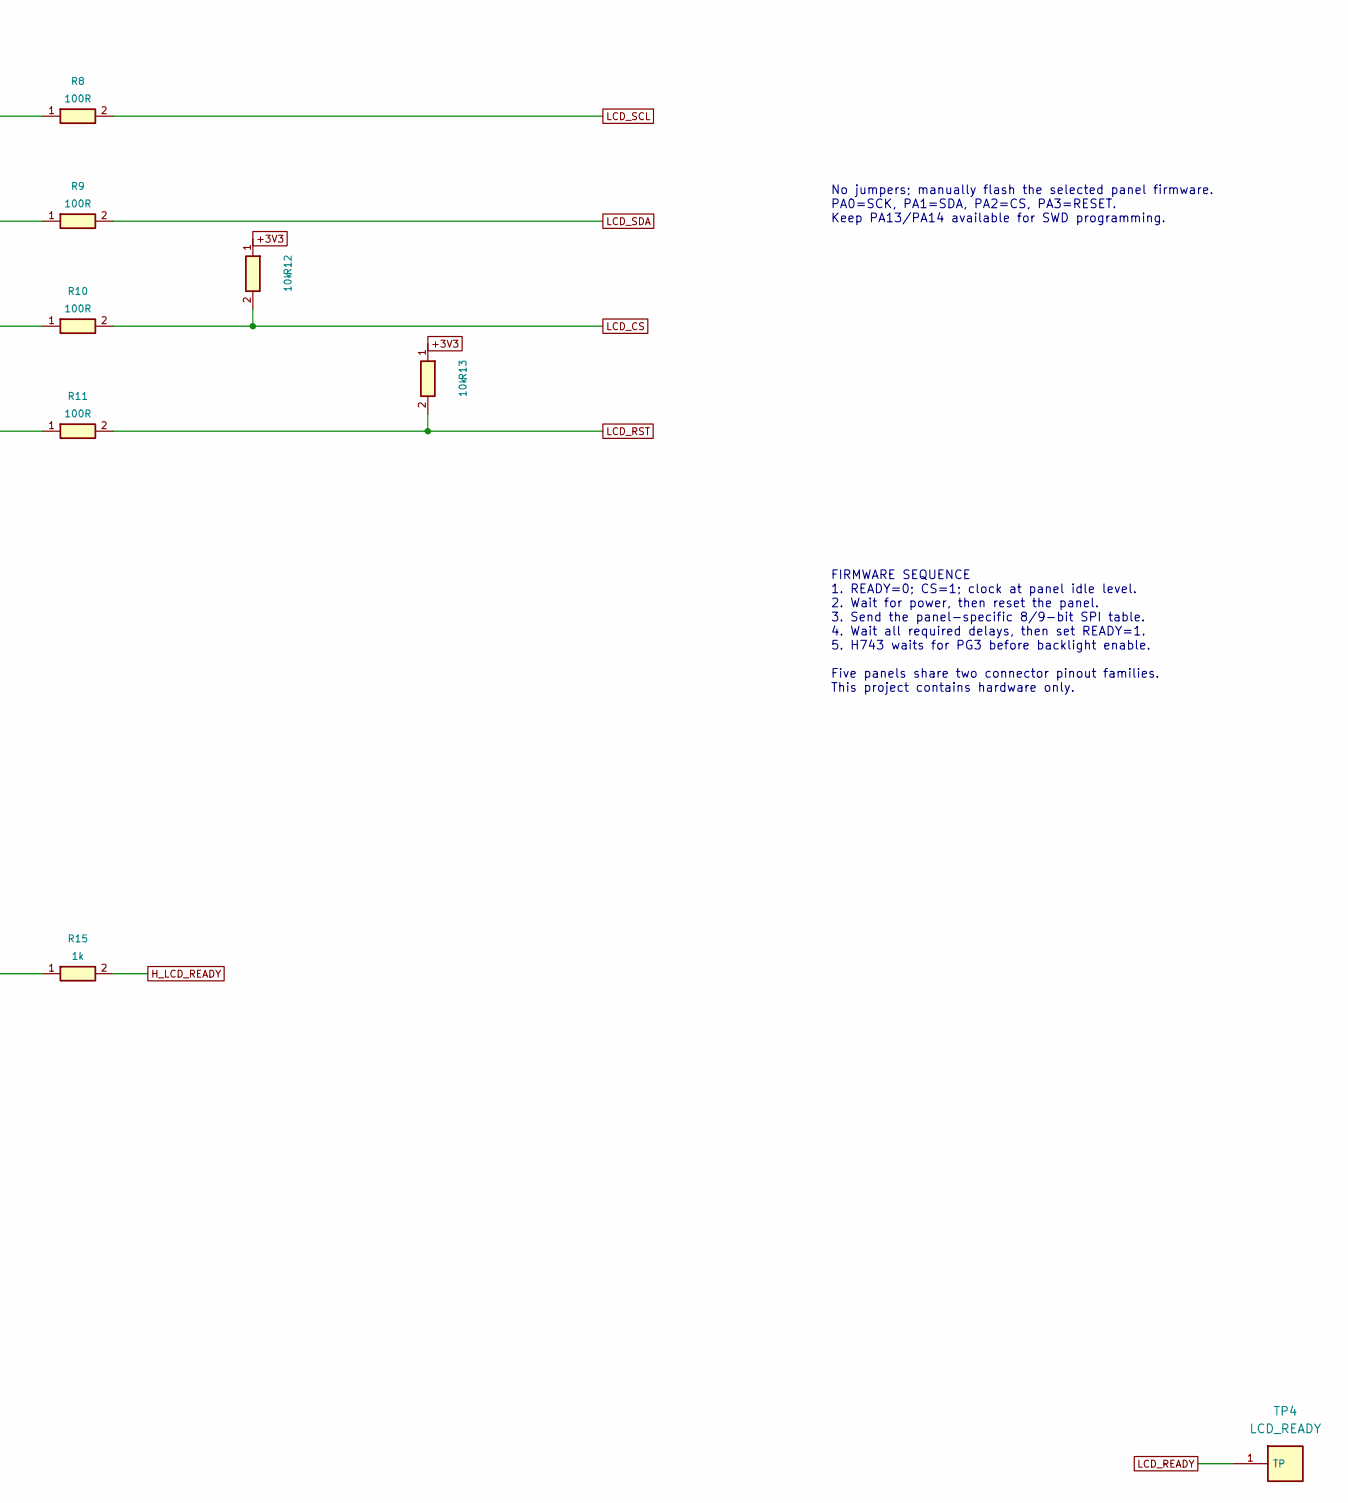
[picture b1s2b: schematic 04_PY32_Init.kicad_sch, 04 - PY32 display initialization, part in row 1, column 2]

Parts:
C13, C14: 100n; C_0603_1608Metric
C15: 1u; C_0603_1608Metric; not fitted
J6: PY32 SWD / 2.54mm; Header1x06
R8, R9, R10, R11: 100R; R_0603_1608Metric
R12, R13, R17: 10k; R_0603_1608Metric
R14: 100k; R_0603_1608Metric
R15: 1k; R_0603_1608Metric
R16: 0R; R_0603_1608Metric; not fitted
TP4: LCD_READY; TestPoint
U3: PY32F002AW15S / SOP16; SOIC16

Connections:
+3V3: C14.1, C15.1, J6.1 (VTREF), R12.1, R13.1, R17.1, U3.4 (VCC); also elsewhere on the board
GND: C13.2, C14.2, C15.2, J6.2 (GND), R14.2, U3.13 (VSS); also elsewhere on the board
H_LCD_READY: R15.2; also elsewhere on the board
H_NRST: R16.1; also elsewhere on the board
LCD_CS: R10.2, R12.2; also elsewhere on the board
LCD_READY: R14.1, R15.1, TP4.1 (TP_1), U3.16 (PA6/READY)
LCD_RST: R11.2, R13.2; also elsewhere on the board
LCD_SCL: R8.2; also elsewhere on the board
LCD_SDA: R9.2; also elsewhere on the board
PY_LCD_CS: R10.1, U3.14 (PA2/LCD_CS)
PY_LCD_RST: R11.1, U3.15 (PA3/LCD_RST)
PY_LCD_SCK: R8.1, U3.11 (PA0/LCD_SCK)
PY_LCD_SDA: R9.1, U3.12 (PA1/LCD_SDA)
PY_NRST: C13.1, J6.5 (NRST), R16.2, R17.2, U3.8 (PF2/NRST)
PY_SWCLK: J6.4 (SWCLK), U3.7 (PA14/SWCLK)
PY_SWDIO: J6.3 (SWDIO), U3.6 (PA13/SWDIO)
PY_TX_LOG: J6.6 (TX_LOG), U3.5 (PA9/TX_LOG)

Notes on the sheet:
RESET / R16 links host reset to PY32
READY TO HOST + BACKLIGHT GATE
No jumpers; manually flash the selected panel firmware. PA0=SCK, PA1=SDA, PA2=CS, PA3=RESET. Keep PA13/PA14 available for SWD programming.
R14 keeps READY low during reset. R15 isolates the host READY input.
PY32F002A / SOFTWARE SPI INITIALIZER / 3.3V
SWD PROGRAMMING
FIRMWARE SEQUENCE 1. READY=0; CS=1; clock at panel idle level. 2. Wait for power, then reset the panel. 3. Send the panel-specific 8/9-bit SPI table. 4. Wait all required delays, then set READY=1. 5. H743 waits for PG3 before backlight enable. Five panels share two connector pinout families. This p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
